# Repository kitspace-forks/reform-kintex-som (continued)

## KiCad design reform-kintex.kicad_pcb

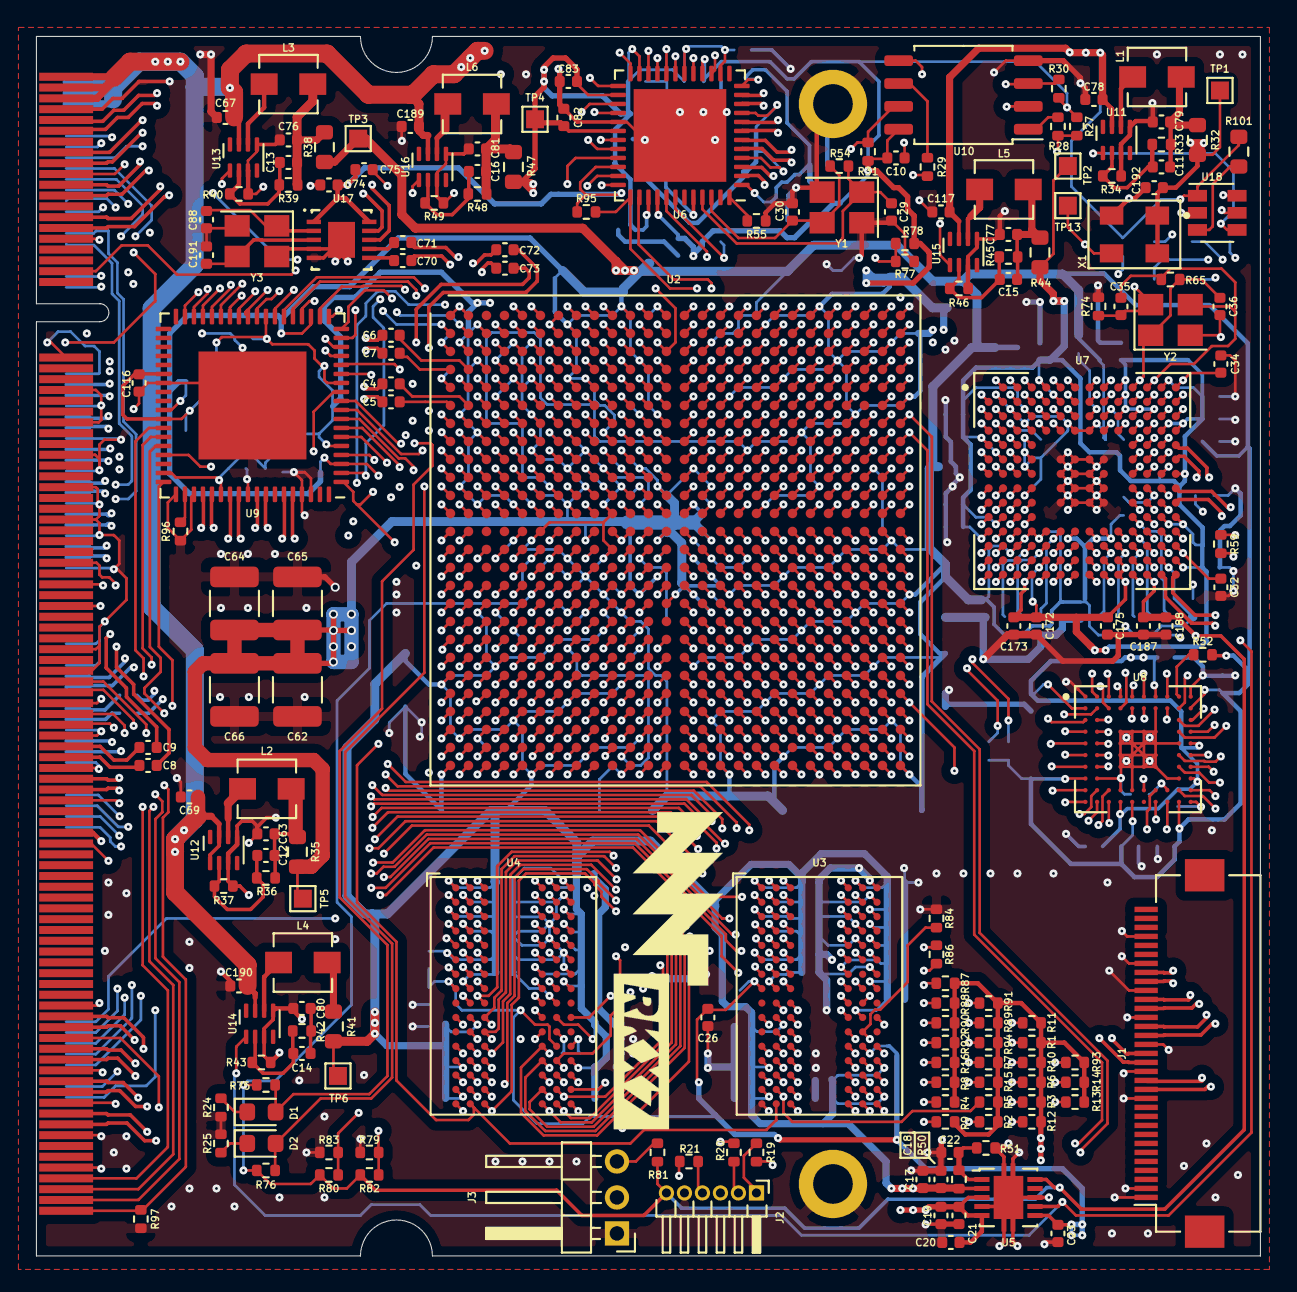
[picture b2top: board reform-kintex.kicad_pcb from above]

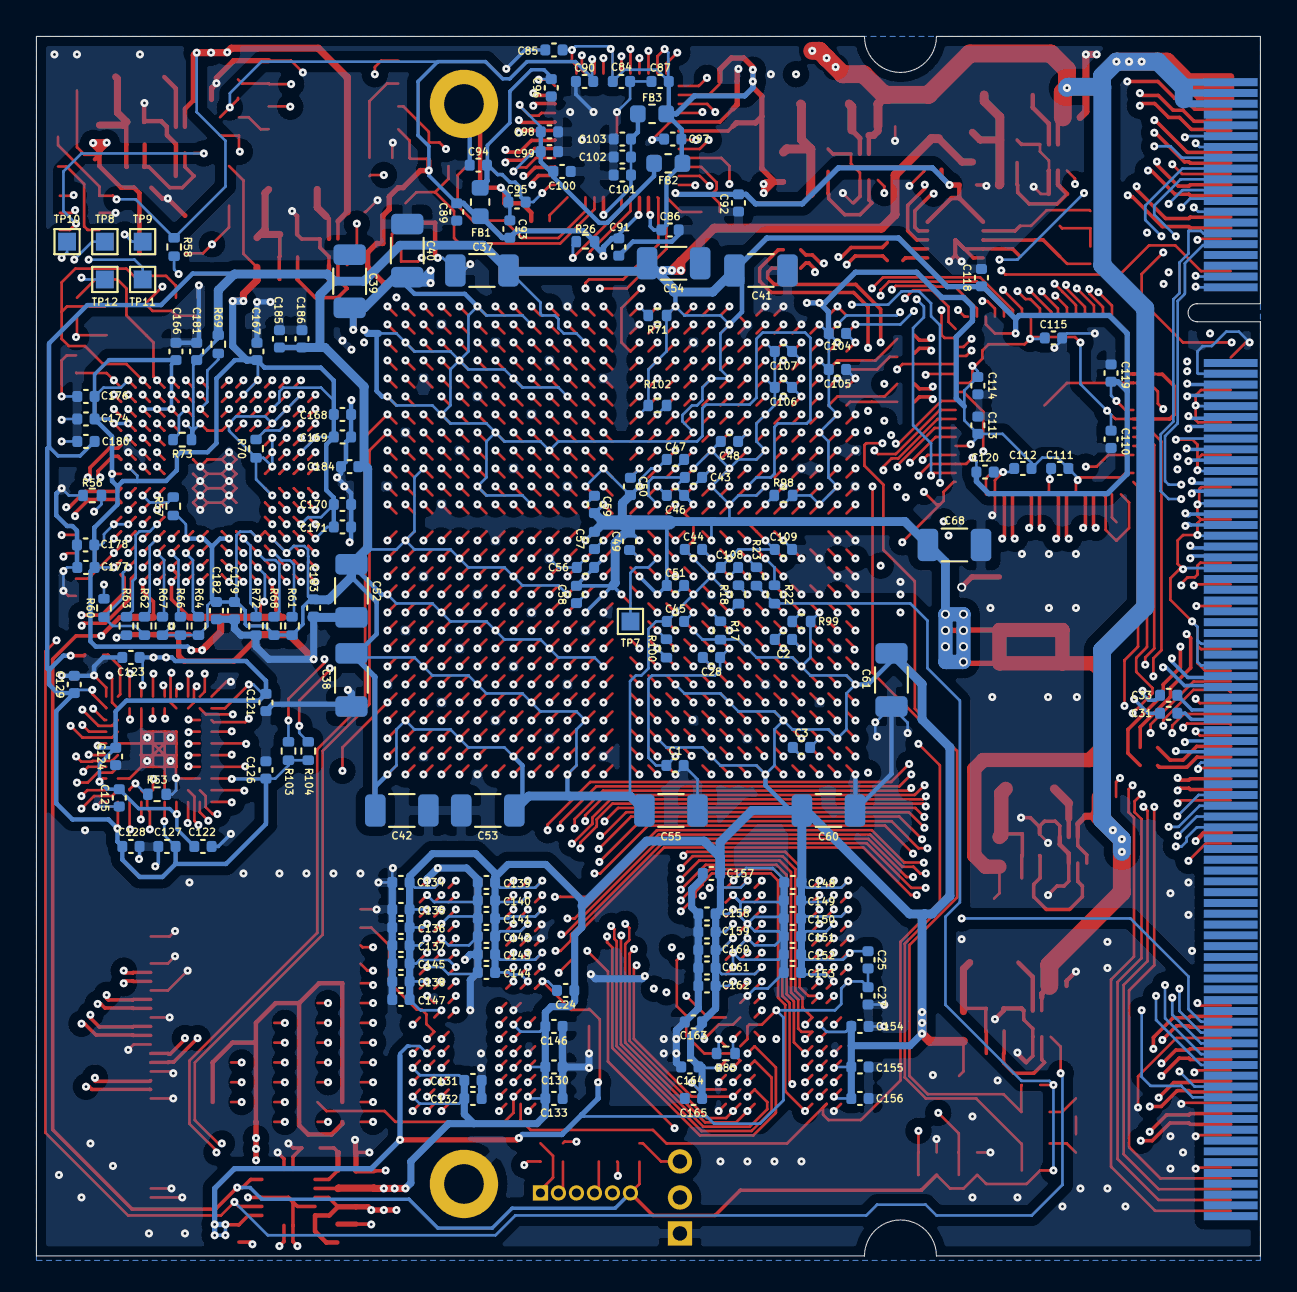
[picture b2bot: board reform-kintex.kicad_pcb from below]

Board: 8 copper layers, 68.0 x 67.8 mm, 348 parts (170 on the bottom side), 416 nets.

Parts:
C1, C2, C3, C4, C5, C6, C7, C8, C9, C10, C23, C28, C31, C33, C70, C71, C72, C73, C74, C83, C84, C85, C86, C87, C90, C91, C92, C95, C96, C99, C100, C102, C110, C111, C112, C113, C114, C115, C116, C118, C119, C120, C121, C122, C123, C124, C125, C126, C127, C128, C129, C130, C131, C132, C133, C134, C135, C136, C137, C138, C139, C140, C141, C142, C143, C144, C145, C146, C147, C148, C149, C150, C151, C152, C153, C154, C155, C156, C157, C158, C159, C160, C161, C162, C163, C164, C165, C167, C168, C169, C170, C171, C172, C173, C174, C175, C176, C177, C178, C180, C181, C182, C183, C184, C185, C186, C188, C192: 0.1uF; C_0402_1005Metric
C11, C12, C13, C14, C15, C16: 120p; C_0402_1005Metric
C17, C18, C19, C20, C21, C63, C76, C77, C79, C80, C81, C82, C89, C93, C94, C97, C98, C101: 10uF; C_0402_1005Metric
C22: 1nF; C_0402_1005Metric
C24, C25, C26, C27, C103: 10nF; C_0402_1005Metric
C29, C30, C35, C36, C88, C191: 22pF; C_0402_1005Metric
C32, C34: 4.7nF; C_0402_1005Metric
C37, C38, C39, C40, C41, C42, C60, C61, C68: 100uF; C_1206_3216Metric
C43, C44, C45, C46, C47, C48, C49, C50, C51, C56, C57, C58, C59, C67, C69, C75, C78, C104, C105, C106, C107, C108, C109, C117, C189, C190: 4.7uF; C_0402_1005Metric
C52, C53, C54, C55: 47uF; C_1206_3216Metric
C62, C64, C65, C66: 220uF; C_1210_3225Metric
C166, C179, C187: 1uF; C_0402_1005Metric
D1, D2: LED_Small; LED_0603_1608Metric
FB1, FB2, FB3: Ferrite_Bead_Small; L_0603_1608Metric
GFX1: MountingHole; mnt-rkx7
H1, H2: MountingHole_Pad; MountingHole_2.2mm_M2_DIN965_Pad
J1: Conn_01x33; Hirose_FH12-33S-0.5SH_1x33-1MP_P0.50mm_Horizontal
J2: JTAG_01x06; PinHeader_1x06_P1.00mm_Horizontal
J3: Conn_01x03_Male; PinHeader_1x03_P2.00mm_Horizontal
L1, L2, L3, L4, L5, L6: IHLP1212AEERR47M11; L_Vishay_IHLP-1212
R1, R2, R3, R4, R5, R6, R7, R8, R9, R10, R11, R12, R13, R14, R15, R16, R87, R88, R89, R90, R91, R92, R93, R94: 40; R_0402_1005Metric
R17, R18, R86, R99, R100: 80.6; R_0402_1005Metric
R19, R20, R21, R77, R98: 100; R_0402_1005Metric
R22, R26, R75, R95: 4.7k; R_0402_1005Metric
R23: ???; R_0402_1005Metric
R24, R25: 200; R_0402_1005Metric
R27: 2k2; R_0402_1005Metric
R28, R29, R79, R80, R81: 0; R_0402_1005Metric
R30, R31, R71, R102, R103, R104: 4k7; R_0402_1005Metric
R32, R35, R38, R41, R44, R47, R101: 0; R_0603_1608Metric
R33: 453k; R_0402_1005Metric
R34, R37, R40, R43, R46, R49: 100k_1%; R_0402_1005Metric
R36: 66.5k; R_0402_1005Metric
R39: 200k; R_0402_1005Metric
R42: 150k; R_0402_1005Metric
R45: 83.5k; R_0402_1005Metric
R48: 100k; R_0402_1005Metric
R50, R51, R52, R53, R56, R57, R97: 10k; R_0402_1005Metric
R54, R65: 1.8M; R_0402_1005Metric
R55: 12.1k; R_0402_1005Metric
R58: 90.9k 1%; R_0402_1005Metric
R59, R60: 10k 1%; R_0402_1005Metric
R61, R62, R63, R64, R66, R67, R68, R69, R70, R72, R73, R74, R78, R82, R83: DNP; R_0402_1005Metric
R76: 330; R_0402_1005Metric
R84, R85: 240 1%; R_0402_1005Metric
R96: 5.1k; R_0402_1005Metric
TP1, TP2, TP3, TP4, TP5, TP6, TP7, TP13: TestPoint; TestPoint_Pad_1.0x1.0mm
TP8: TUSBJ_TCK; TestPoint_Pad_1.0x1.0mm
TP9: TUSBJ_TMS; TestPoint_Pad_1.0x1.0mm
TP10: TUSBJ_TDI; TestPoint_Pad_1.0x1.0mm
TP11: TUSBJ_TRSTN; TestPoint_Pad_1.0x1.0mm
TP12: TUSBJ_TDO; TestPoint_Pad_1.0x1.0mm
U1: MNT Reform 2.0 SoM Socket; ddr2-sodimm200
U2: XC7K160T-FFG676; Xilinx_FFG676
U3, U4: IS43TR16512B-125KBLI; BGA-96_9.0x13.0mm_Layout2x3x16_P0.8mm
U5: TPS51200DRC; VSON-10-1EP_3x3mm_P0.5mm_EP1.65x2.4mm
U6: KSZ9031RNXCA; QFN-48-1EP_7x7mm_P0.5mm_EP5.15x5.15mm
U7: TUSB1310ZAY; BGA175C80P14X14_1200X1200X140
U8: TC358778XBG; BGA80C65P10X10_700X700X100
U9: SiI9022A; QFN-72-1EP_10x10mm_P0.5mm_EP6x6mm
U10: W25Q128JVS; SOIC-8_5.23x5.23mm_P1.27mm
U11, U12, U13, U14, U15, U16: TPS62823DLC; Texas_VSON-HR-8_1.5x2mm_P0.5mm
U17: Si52112-B5-GM2; Silicon_Labs-Si52112-B5-GM2-Level_B
U18: LM3880; SOT-23-6
X1: ASFLMB-100.000MHZ-XY-T; OSCDFN500X320X90-4N
Y1, Y3: ABM8G-25.000MHZ-18-D2Y-T; Crystal_SMD_3225-4Pin_3.2x2.5mm
Y2: ABM8G-20.000MHZ-18-D2Y-T; Crystal_SMD_3225-4Pin_3.2x2.5mm

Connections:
+1V0: C47.2, C48.2, C49.2, C50.2, C51.2, C56.2, C57.2, C58.2, C59.2, C62.2, C64.2, C65.2, C66.2, C68.2, C106.2, C107.2, R35.1, TP5.1, U2.C6, U2.E6, U2.G6, U2.J6, U2.J9, U2.K8, U2.K10, U2.K12, U2.K14, U2.L6, U2.L9, U2.L13, U2.L15, U2.M8, U2.M14, U2.N9, U2.N13, U2.N15, U2.P14, U2.R13, U2.R15, U2.T12, U2.T14, U2.U13, U2.U15
+1V1: C166.1, C167.1, C168.1, C169.1, C170.1, C171.1, C172.1, C173.1, C174.1, C175.1, C176.1, C177.1, C178.1, R44.1, TP2.1, U7.A5, U7.A10, U7.A13, U7.B6, U7.B10, U7.C4, U7.C10, U7.C11, U7.C12, U7.D13, U7.D14, U7.E1, U7.F2, U7.G13, U7.G14, U7.K2, U7.K13, U7.K14, U7.L1, U7.N5, U7.N10, U7.N14, U7.P4, U7.P10
+1V2: C82.2, C83.2, C84.2, C85.2, C86.2, C87.2, C97.2, C104.2, C105.2, C110.1, C111.1, C112.1, C113.1, C114.1, C115.1, C116.1, C121.1, C122.1, C123.1, C124.1, C125.1, FB2.2, FB3.2, R47.1, R98.2, TP4.1, U2.B3, U2.C2, U2.D3, U2.G2, U2.H3, U2.L2, U2.M3, U2.M5, U6.14, U6.18, U6.23, U6.26, U6.30, U6.39, U8.A7, U8.B1, U8.E10, U8.H10, U8.K4, U9.5, U9.12, U9.26, U9.42, U9.47, U9.53, U9.60
+1V5: C17.1, C18.1, C24.1, C25.1, C60.2, C61.2, C130.1, C131.1, C132.1, C133.1, C134.1, C135.1, C136.1, C137.1, C138.1, C139.1, C140.1, C141.1, C142.1, C143.1, C144.1, C145.1, C146.1, C147.1, C148.1, C149.1, C150.1, C151.1, C152.1, C153.1, C154.1, C155.1, C156.1, C157.1, C158.1, C159.1, C160.1, C161.1, C162.1, C163.1, C164.1, C165.1, R17.2, R41.1, R50.1, R99.2, TP6.1, U2.AA1, U2.AA11, U2.AB8, U2.AC5, U2.AD2, U2.AD12, U2.AE9, U2.AF6, U2.U3, U2.V10, U2.W7, U2.Y4, U3.A1, U3.A8, U3.B2, U3.C1, U3.C9, U3.D2, U3.D9, U3.E9, U3.F1, U3.G7, U3.H2, U3.H9, U3.K2, U3.K8, U3.N1, U3.N9, U3.R1, U3.R9, U4.A1, U4.A8, U4.B2, U4.C1, U4.C9, U4.D2, U4.D9, U4.E9, U4.F1, U4.G7, U4.H2, U4.H9, U4.K2, U4.K8, U4.N1, U4.N9, U4.R1, U4.R9, U5.2
+1V8: C37.2, C38.2, C41.2, C42.2, C43.2, C44.2, C45.2, C46.2, C52.2, C53.2, C54.2, C55.2, C108.2, C109.2, C118.1, C119.1, C120.1, C126.1, C127.1, C128.1, C129.1, C179.1, C180.1, C181.1, C182.1, C183.1, C184.1, C185.1, C186.1, R38.1, R52.1, R57.1, R61.1, R63.1, R64.1, R66.1, R67.1, R68.1, R69.1, R70.1, R71.1, R73.1, R102.1, R103.1, R104.1, TP3.1, U2.A11, U2.AA21, U2.AB18, U2.AC15, U2.AC25, U2.AD22, U2.AE19, U2.AF16, U2.AF26, U2.B8, U2.C15, U2.D12, U2.E8, U2.E9, U2.G13, U2.H10, U2.K24, U2.L11, U2.M10, U2.M12, U2.N6, U2.N25, U2.P8, U2.P10, U2.P22, U2.R9, U2.R19, U2.T8, U2.T10, U2.T16, U2.T26, U2.U11, U2.U23, U2.V20, U2.W17, U2.Y14, U2.Y24, U7.B2, U7.C3, U7.D4, U7.D7, U7.D8, U7.D9, U7.E4, U7.F4, U7.G4, U7.H4, U7.L4, U7.L5, U7.L7, U7.L8, U7.L9, U7.M3, U8.B10, U8.H1, U8.K5, U8.K9, U9.3, U9.21, U9.46
+3V3: C10.1, C39.2, C40.2, C74.2, C75.2, C89.2, C90.2, C91.2, C92.2, C93.2, C187.1, C188.1, C192.1, FB1.2, J2.6, R22.1, R23.1, R26.1, R27.1, R30.1, R31.1, R32.1, R75.1, R76.1, R77.1, R79.1, R80.1, R81.1, R95.1, TP1.1, U2.A21, U2.B18, U2.C25, U2.D22, U2.E19, U2.F16, U2.F26, U2.G23, U2.H20, U2.J17, U2.L7, U2.L21, U2.M18, U2.T6, U5.10, U6.16, U6.34, U6.40, U7.P12, U10.8, U17.1, U17.10, X1.1, X1.4
+5V: C67.2, C69.2, C78.2, C117.2, C189.2, C190.2, R58.2, R101.1, U1.1, U1.2, U1.3, U1.4, U1.5, U1.6, U11.7, U12.1, U12.7, U13.7, U14.7, U15.7, U16.7, U18.1
/RAM/PCIE2_GTX_CLK_HOST_N: C71.2, U2.D5
/RAM/PCIE2_GTX_CLK_HOST_P: C70.2, U2.D6
/RAM/PCIE2_GTX_CLK_N: C73.2, U2.F5
/RAM/PCIE2_GTX_CLK_P: C72.2, U2.F6
/RAM/USB1TXN: C31.2, U7.H14
/RAM/USB1TXP: C33.2, U7.J14
/RAM/USB2_GTX_N: C8.2, U2.B1
/RAM/USB2_GTX_P: C9.2, U2.B2
BACKLIGHT_EN: U1.105, U2.B16
BACKLIGHT_PWM: U1.164, U2.K16
CCLK: R29.2, U2.C8
CLK_100MHZ: TP13.1, U2.F22, X1.3
DAC_BCLK: U1.170, U2.L17
DAC_DIN: U1.166, U2.K17
DAC_DOUT: U1.178, U2.M17
DAC_MCLK: U1.176, U2.L18
DAC_RXFS: U1.168, U2.K18
DAC_SCL: U1.101, U2.H26
DAC_SDA: U1.103, U2.G26
DAC_TXFS: U1.172, U2.M16
DISP1_CLK: U2.C12, U9.22
DISP1_DE: U2.D10, U9.33
DISP1_HS: U2.D11, U9.34
DISP1_RGB0: U2.E10, U9.32
DISP1_RGB1: U2.D8, U9.31
DISP1_RGB2: U2.F9, U9.30
DISP1_RGB3: U2.F8, U9.29
DISP1_RGB4: U2.A9, U9.28
DISP1_RGB5: U2.A8, U9.27
DISP1_RGB6: U2.B9, U9.25
DISP1_RGB7: U2.D9, U9.24
DISP1_RGB8: U2.F14, U9.23
DISP1_RGB9: U2.C9, U9.20
DISP1_RGB10: U2.G14, U9.19
DISP1_RGB11: U2.F10, U9.18
DISP1_RGB12: U2.H14, U9.17
DISP1_RGB13: U2.G11, U9.16
DISP1_RGB14: U2.H11, U9.15
DISP1_RGB15: U2.G9, U9.14
DISP1_RGB16: U2.H13, U9.13
DISP1_RGB17: U2.G10, U9.11
DISP1_RGB18: U2.J13, U9.10
DISP1_RGB19: U2.H12, U9.9
DISP1_RGB20: U2.J10, U9.8
DISP1_RGB21: U2.H8, U9.7
DISP1_RGB22: U2.H9, U9.6
DISP1_RGB23: U2.J11, U9.4
DISP1_SCL: R102.2, U1.107, U2.G12, U9.1
DISP1_SDA: R71.2, U1.109, U2.A13, U9.2
DISP1_VS: U2.E11, U9.35
DISP2_DE: U2.AA15, U8.J7
DISP2_HS: U2.AB15, U8.K8
DISP2_PCLK: U2.AC18, U8.J6
DISP2_RGB0: U2.AF15, U8.J3
DISP2_RGB1: U2.AF14, U8.K3
DISP2_RGB2: U2.AE16, U8.J2
DISP2_RGB3: U2.AE15, U8.K2
DISP2_RGB4: U2.AE17, U8.J1
DISP2_RGB5: U2.AF17, U8.K1
DISP2_RGB6: U2.AA14, U8.G2
DISP2_RGB7: U2.AF18, U8.G1
DISP2_RGB8: U2.AD15, U8.F2
DISP2_RGB9: U2.AE18, U8.F1
DISP2_RGB10: U2.AD16, U8.E2
DISP2_RGB11: U2.AF19, U8.E1
DISP2_RGB12: U2.AC16, U8.D2
DISP2_RGB13: U2.AD14, U8.D1
DISP2_RGB14: U2.AC17, U8.C2
DISP2_RGB15: U2.AC14, U8.C1
DISP2_RGB16: U2.AB14, U8.B2
DISP2_RGB17: U2.AA17, U8.A2
DISP2_RGB18: U2.Y15, U8.B3
DISP2_RGB19: U2.AA18, U8.A3
DISP2_RGB20: U2.Y16, U8.B4
DISP2_RGB21: U2.AB17, U8.A4
DISP2_RGB22: U2.AF20, U8.B5
DISP2_RGB23: U2.AD20, U8.A5
DISP2_SCL: R104.2, U2.Y26, U8.A8
DISP2_SDA: R103.2, U2.W26, U8.B8
DISP2_VS: U2.AB16, U8.K7
DSI_CLK_N: J1.19, U8.F10
DSI_CLK_P: J1.20, U8.F9
DSI_D0_N: J1.25, U8.J10
DSI_D0_P: J1.26, U8.J9
DSI_D1_N: J1.22, U8.G10
DSI_D1_P: J1.23, U8.G9
DSI_D2_N: J1.16, U8.D10
DSI_D2_P: J1.17, U8.D9
DSI_D3_N: J1.13, U8.C10
DSI_D3_P: J1.14, U8.C9
DSI_RST_N: U2.AB26, U8.B9
EDP_RESETn: U1.38, U2.C14
EN_VAUX: U15.1, U18.6
EN_VDDR: U5.7, U14.1, U18.5
EN_VIO: U11.1, U13.1, U16.1, U18.4
ETH0_A+: U1.29, U6.2
ETH0_A-: U1.27, U6.3
ETH0_B+: U1.23, U6.5
ETH0_B-: U1.21, U6.6
ETH0_C+: U1.17, U6.7
ETH0_C-: U1.15, U6.8
ETH0_D+: U1.11, U6.10
ETH0_D-: U1.9, U6.11
ETH0_LED_LINK1: U1.83, U6.17
ETH0_LED_RX: U1.79, U6.15
ETH_INT_N: U2.E16, U6.38
ETH_MDC: U2.E17, U6.36
ETH_MDIO: R95.2, U2.E15, U6.37
ETH_REF_CLK: U2.F17, U6.41
ETH_RST_N: R26.2, U2.G17, U6.42
ETH_RX_CLK: U2.D18, U6.35
ETH_RX_D0: U2.J15, U6.32
ETH_RX_D1: U2.J16, U6.31
ETH_RX_D2: U2.F20, U6.28
ETH_RX_D3: U2.D20, U6.27
ETH_RX_DV: U2.F15, U6.33
ETH_TX_CLK: U2.E18, U6.24
ETH_TX_D0: U2.H18, U6.19
ETH_TX_D1: U2.H17, U6.20
ETH_TX_D2: U2.G19, U6.21
ETH_TX_D3: U2.F18, U6.22
ETH_TX_EN: U2.D19, U6.25
ETH_VDDA: C94.2, C95.2, C96.2, FB1.1, U6.1, U6.12
ETH_VDDL: C98.2, C99.2, C100.2, FB2.1, U6.4, U6.9
ETH_VDDL_PLL: C101.2, C102.2, C103.2, FB3.1, U6.44
FCS_B: R27.2, R28.2, U2.C23
GND: C1.1, C2.1, C3.1, C10.2, C17.2, C18.2, C19.2, C20.2, C21.2, C22.2, C23.2, C26.2, C27.2, C28.1, C29.2, C30.2, C32.2, C34.2, C37.1, C38.1, C39.1, C40.1, C41.1, C42.1, C43.1, C44.1, C45.1, C46.1, C47.1, C48.1, C49.1, C50.1, C51.1, C52.1, C53.1, C54.1, C55.1, C56.1, C57.1, C58.1, C59.1, C60.1, C61.1, C62.1, C63.2, C64.1, C65.1, C66.1, C67.1, C68.1, C69.1, C74.1, C75.1, C76.2, C77.2, C78.1, C79.2, C80.2, C81.2, C82.1, C83.1, C84.1, C85.1, C86.1, C87.1, C88.2, C89.1, C90.1, C91.1, C92.1, C93.1, C94.1, C95.1, C96.1, C97.1, C98.1, C99.1, C100.1, C101.1, C102.1, C103.1, C104.1, C105.1, C106.1, C107.1, C108.1, C109.1, C110.2, C111.2, C112.2, C113.2, C114.2, C115.2, C116.2, C117.1, C118.2, C119.2, C120.2, C121.2, C122.2, C123.2, C124.2, C125.2, C126.2, C127.2, C128.2, C129.2, C130.2, C131.2, C132.2, C133.2, C134.2, C135.2, C136.2, C137.2, C138.2, C139.2, C140.2, C141.2, C142.2, C143.2, C144.2, C145.2, C146.2, C147.2, C148.2, C149.2, C150.2, C151.2, C152.2, C153.2, C154.2, C155.2, C156.2, C157.2, C158.2, C159.2, C160.2, C161.2, C162.2, C163.2, C164.2, C165.2, C166.2, C167.2, C168.2, C169.2, C170.2, C171.2, C172.2, C173.2, C174.2, C175.2, C176.2, C177.2, C178.2, C179.2, C180.2, C181.2, C182.2, C183.2, C184.2, C185.2, C186.2, C187.2, C188.2, C189.1, C190.1, C191.2, C192.2, H1.1, H2.1, J1.1, J1.2, J1.12, J1.15, J1.18, J1.21, J1.24, J1.27, J1.30, J2.5, J3.1, R18.1, R24.1, R25.1, R34.2, R37.2, R40.2, R43.2, R46.2, R49.2, R51.1, R53.2, R55.2, R56.1, R60.1, R62.1, R72.1, R74.1, R78.2, R82.2, R83.2, R84.2, R85.2, R96.1, R97.2, R100.1, U1.7, U1.19, U1.31, U1.41, U1.44, U1.47, U1.50, U1.53, U1.56, U1.59, U1.62, U1.65, U1.68, U1.71, U1.74, U1.80, U1.94, U1.95, U1.98, U1.99, U1.110, U1.111, U1.116, U1.117, U1.123, U1.129, U1.161, U1.167, U1.173, U1.179, U1.185, U1.191, U2.A1, U2.A2, U2.A5, U2.A6, U2.A7, U2.A16, U2.A26, U2.AA6, U2.AA16, U2.AA26, U2.AB3, U2.AB13, U2.AB23, U2.AC10, U2.AC20, U2.AD7, U2.AD17, U2.AE4, U2.AE14, U2.AE24, U2.AF1, U2.AF11, U2.AF21, U2.B4, U2.B7, U2.B13, U2.B23, U2.C1, U2.C5, U2.C7, U2.C10, U2.C20, U2.D4, U2.D7, U2.D17, U2.E1, U2.E2, U2.E5, U2.E7, U2.E14, U2.E24, U2.F3, U2.F4, U2.F7, U2.F11, U2.F21, U2.G1, U2.G5, U2.G8, U2.G18, U2.H4, U2.H7, U2.H15, U2.H25, U2.J1, U2.J2, U2.J5, U2.J12, U2.J22, U2.K3, U2.K4, U2.K7, U2.K9, U2.K11, U2.K13, U2.K19, U2.L1, U2.L5, U2.L10, U2.L12, U2.L14, U2.L16, U2.L26, U2.M4, U2.M7, U2.M9, U2.M13, U2.M15, U2.M23, U2.N1, U2.N2, U2.N5, U2.N7, U2.N10, U2.N11, U2.N12, U2.N14, U2.N20, U2.P3, U2.P4, U2.P9, U2.P11, U2.P13, U2.P15, U2.P17, U2.R1, U2.R2, U2.R5, U2.R8, U2.R10, U2.R11, U2.R12, U2.R14, U2.R24, U2.T1, U2.T3, U2.T4, U2.T9, U2.T11, U2.T13, U2.T15, U2.T21, U2.U8, U2.U10, U2.U12, U2.U14, U2.U18, U2.V5, U2.V15, U2.V25, U2.W2, U2.W12, U2.W22, U2.Y9, U2.Y19, U3.A9, U3.B1, U3.B3, U3.B9, U3.D1, U3.D8, U3.E1, U3.E2, U3.E8, U3.F9, U3.G1, U3.G9, U3.J2, U3.J8, U3.M1, U3.M9, U3.P1, U3.P9, U3.T1, U3.T9, U4.A9, U4.B1, U4.B3, U4.B9, U4.D1, U4.D8, U4.E1, U4.E2, U4.E8, U4.F9, U4.G1, U4.G9, U4.J2, U4.J8, U4.M1, U4.M9, U4.P1, U4.P9, U4.T1, U4.T9, U5.4, U5.8, U5.11, U6.29, U6.49, U7.B11, U7.B13, U7.B14, U7.D12, U7.E13, U7.F6, U7.F7, U7.F8, U7.F9, U7.F12, U7.F13, U7.G6, U7.G7, U7.G8, U7.G9, U7.G12, U7.H6, U7.H7, U7.H8, U7.H9, U7.H13, U7.J6, U7.J7, U7.J8, U7.J9, U7.J13, U7.K12, U7.L12, U7.M12, U7.M13, U7.N13, U8.A1, U8.A10, U8.B7, U8.D4, U8.D5, U8.D6, U8.D7, U8.E4, U8.E5, U8.E6, U8.E7, U8.E9, U8.F4, U8.F5, U8.F6, U8.F7, U8.G4, U8.G5, U8.G6, U8.G7, U8.H2, U8.H9, U8.J4, U8.J5, U8.K10, U9.43, U9.55, U9.57, U9.63, U9.69, U9.70, U9.73, U10.4, U11.3, U11.5, U12.3, U12.5, U13.3, U13.5, U14.3, U14.5, U15.3, U15.5, U16.3, U16.5, U17.4, U17.5, U18.2, X1.2, Y1.2, Y1.4, Y3.2, Y3.4
HDMI_CEC: U1.197, U9.50
HDMI_CLK+: U1.165, U9.58
HDMI_CLK-: U1.163, U9.59
HDMI_D0+: U1.171, U9.62
HDMI_D0-: U1.169, U9.61
HDMI_D1+: U1.177, U9.65
HDMI_D1-: U1.175, U9.64
HDMI_D2+: U1.183, U9.68
HDMI_D2-: U1.181, U9.67
HDMI_HPD: R97.1, U1.199, U9.54
HDMI_RST_N: U2.C13, U9.51
HDMI_SCL: U1.195, U9.49
HDMI_SDA: U1.193, U9.48
MODE0: R79.2, R82.1, U2.T5
MODE1: R80.2, R83.1, U2.T2
MODE2: J3.2, U2.P5
unnamed: C4.2, U2.F2
unnamed: C5.2, U2.F1
unnamed: C6.2, U2.D2
unnamed: C7.2, U2.D1
unnamed: C11.1, C79.1, L1.2, R32.2, R33.1
unnamed: C11.2, R33.2, R34.1, U11.2
unnamed: C12.1, C63.1, L2.2, R35.2, R36.1
unnamed: C12.2, R36.2, R37.1, U12.2
unnamed: C13.1, C76.1, L3.2, R38.2, R39.1
unnamed: C13.2, R39.2, R40.1, U13.2
unnamed: C14.1, C80.1, L4.2, R41.2, R42.1
unnamed: C14.2, R42.2, R43.1, U14.2
unnamed: C15.1, C77.1, L5.2, R44.2, R45.1
unnamed: C15.2, R45.2, R46.1, U15.2
unnamed: C16.1, C81.1, L6.2, R47.2, R48.1
unnamed: C16.2, R48.2, R49.1, U16.2
unnamed: C22.1, R50.2, R51.2, U5.1
unnamed: C29.1, R54.2, U6.45, Y1.1
unnamed: C30.1, R54.1, U6.46, Y1.3
unnamed: C32.1, U7.M14
unnamed: C34.1, U7.A14
unnamed: C35.1, R65.1, U7.A12, Y2.3
unnamed: C36.1, R65.2, U7.A11, Y2.1
unnamed: C88.1, U17.2, Y3.1
unnamed: C191.1, U17.3, Y3.3
unnamed: D1.1, R24.2
unnamed: D1.2, R75.2, U2.G7
unnamed: D2.1, R25.2
unnamed: D2.2, R76.2, U2.J7
unnamed: J2.1, R19.2
unnamed: J2.2, R20.2
unnamed: J2.3, U2.R7
unnamed: J2.4, R21.2
unnamed: J3.3, R81.2
unnamed: L1.1, U11.6
unnamed: L2.1, U12.6
unnamed: L3.1, U13.6
unnamed: L4.1, U14.6
unnamed: L5.1, U15.6
unnamed: L6.1, U16.6
unnamed: R17.1, U2.U9
unnamed: R18.2, U2.T7
unnamed: R19.1, U2.N8
unnamed: R20.1, U2.R6
unnamed: R21.1, U2.L8
unnamed: R23.2, U2.P7
unnamed: R28.1, U10.1
unnamed: R29.1, U10.6
unnamed: R52.2, U8.A9
unnamed: R53.1, U8.J8
unnamed: R55.1, U6.48
unnamed: R56.2, U7.J12
unnamed: R57.2, U7.H12
unnamed: R58.1, R60.2, U7.N12
unnamed: R59.1, U7.L14
unnamed: R59.2, U7.L13
unnamed: R61.2, U7.M4
unnamed: R62.2, U7.L11
unnamed: R63.2, U7.K11
unnamed: R64.2, U7.M9
unnamed: R66.2, U7.M10
unnamed: R67.2, U7.M11
unnamed: R68.2, U7.M5
unnamed: R69.2, U7.C8
unnamed: R70.2, U7.D3
unnamed: R72.2, U7.L6
unnamed: R73.2, U7.C9
unnamed: R84.1, U3.L8
unnamed: R85.1, U4.L8
unnamed: R96.2, U9.56
unnamed: R98.1, U2.M6
unnamed: R99.1, U2.U4
unnamed: R100.2, U2.V12
unnamed: R101.2, U18.3
unnamed: TP8.1, U7.G11
unnamed: TP9.1, U7.D11
unnamed: TP10.1, U7.E11
unnamed: TP11.1, U7.E12
unnamed: TP12.1, U7.F11
PCIE1_CLK_HOST_N: C71.1, U17.7
PCIE1_CLK_HOST_P: C70.1, U17.6
PCIE1_CLK_N: U1.60, U17.9
PCIE1_CLK_P: U1.58, U17.8
PCIE1_RESETn: U1.37, U2.A17
PCIE1_RX_N: U1.54, U2.G3
PCIE1_RX_P: U1.52, U2.G4
PCIE1_TX_N: C5.1, U1.48
PCIE1_TX_P: C4.1, U1.46
PCIE2_CLK_N: C73.1, U1.66
PCIE2_CLK_P: C72.1, U1.64
PCIE2_RESETn: U1.24, U2.A18
PCIE2_RX_N: U1.78, U2.E3
PCIE2_RX_P: U1.76, U2.E4
PCIE2_TX_N: C7.1, U1.72
PCIE2_TX_P: C6.1, U1.70
PUDC_B: R77.2, R78.1, U2.B25
QSPI_DQ0: U2.B24, U10.5
QSPI_DQ1: U2.A25, U10.2
QSPI_DQ2: R30.2, U2.B22, U10.3
QSPI_DQ3: R31.2, U2.A22, U10.7
RAM_A0: R16.2, U2.AC8, U3.N3, U4.N3
RAM_A1: R8.2, U2.AA7, U3.P7, U4.P7
RAM_A2: R15.2, U2.AA8, U3.P3, U4.P3
RAM_A3: R7.2, U2.AF7, U3.N2, U4.N2
RAM_A4: R14.2, U2.AE7, U3.P8, U4.P8
RAM_A5: R6.2, U2.AC11, U3.P2, U4.P2
RAM_A6: R13.2, U2.V9, U3.R8, U4.R8
RAM_A7: R5.2, U2.Y10, U3.R2, U4.R2
RAM_A8: R12.2, U2.AB11, U3.T8, U4.T8
RAM_A9: R4.2, U2.Y7, U3.R3, U4.R3
RAM_A10: R11.2, U2.Y8, U3.L7, U4.L7
RAM_A11: R3.2, U2.V11, U3.R7, U4.R7
RAM_A12: R10.2, U2.V8, U3.N7, U4.N7
RAM_A13: R2.2, U2.W11, U3.T3, U4.T3
RAM_A14: R9.2, U2.Y11, U3.T7, U4.T7
RAM_A15: R1.2, U2.V7, U3.M7, U4.M7
RAM_BA0: R92.2, U2.AC7, U3.M2, U4.M2
RAM_BA1: R93.2, U2.AB7, U3.N8, U4.N8
RAM_BA2: R94.2, U2.AB9, U3.M3, U4.M3
RAM_CAS#: R88.2, U2.AD8, U3.K3, U4.K3
RAM_CK+: R86.2, U2.W10, U3.J7, U4.J7
RAM_CK-: R86.1, U2.W9, U3.K7, U4.K7
RAM_CKE: R91.2, U2.AB12, U3.K9, U4.K9
RAM_CS#: R90.2, U2.AD9, U3.L2, U4.L2
RAM_D0: U2.V4, U3.E3
RAM_D1: U2.W3, U3.F7
RAM_D2: U2.U5, U3.F2
RAM_D3: U2.Y1, U3.F8
RAM_D4: U2.U7, U3.H3
RAM_D5: U2.W1, U3.H8
RAM_D6: U2.V6, U3.G2
RAM_D7: U2.V2, U3.H7
RAM_D8: U2.Y2, U3.D7
RAM_D9: U2.U1, U3.C3
RAM_D10: U2.AA3, U3.C8
RAM_D11: U2.V3, U3.C2
RAM_D12: U2.AC2, U3.A7
RAM_D13: U2.U2, U3.A2
RAM_D14: U2.AB2, U3.B8
RAM_D15: U2.V1, U3.A3
RAM_D16: U2.AA4, U4.E3
RAM_D17: U2.AB4, U4.H3
RAM_D18: U2.AC4, U4.F7
RAM_D19: U2.AC3, U4.F2
RAM_D20: U2.AC6, U4.F8
RAM_D21: U2.Y6, U4.H8
RAM_D22: U2.Y5, U4.G2
RAM_D23: U2.AD6, U4.H7
RAM_D24: U2.AD1, U4.C3
RAM_D25: U2.AE1, U4.A2
RAM_D26: U2.AE3, U4.B8
RAM_D27: U2.AE2, U4.A3
RAM_D28: U2.AE6, U4.A7
RAM_D29: U2.AE5, U4.D7
RAM_D30: U2.AF3, U4.C8
RAM_D31: U2.AF2, U4.C2
RAM_DM0: U2.U6, U3.E7
RAM_DM1: U2.AD5, U3.D3
RAM_DM2: U2.AB6, U4.E7
RAM_DM3: U2.AD4, U4.D3
RAM_DQS0+: U2.W6, U3.F3
RAM_DQS0-: U2.W5, U3.G3
RAM_DQS1+: U2.AB1, U3.C7
RAM_DQS1-: U2.AC1, U3.B7
RAM_DQS2+: U2.AA5, U4.F3
RAM_DQS2-: U2.AB5, U4.G3
RAM_DQS3+: U2.AF5, U4.C7
RAM_DQS3-: U2.AF4, U4.B7
RAM_ODT: U2.AC12, U3.K1, U4.K1
RAM_RAS#: R87.2, U2.AA9, U3.J3, U4.J3
RAM_RESET#: U2.AA2, U3.T2, U4.T2
RAM_WE#: R89.2, U2.AC9, U3.L3, U4.L3
SD2_CD: U1.26, U2.A10
SD2_CLK: U1.22, U2.C11
SD2_CMD: U1.20, U2.A15
SD2_DATA0: U1.12, U2.A14
SD2_DATA1: U1.14, U2.B10
SD2_DATA2: U1.16, U2.A12
SD2_DATA3: U1.18, U2.B15
SOC_RESETn: R22.2, U1.87, U2.P6
TUSB_CLKOUT: U2.Y23, U7.D10
TUSB_ENAB: U2.AD25, U7.L10
TUSB_PCLK: U2.R21, U7.A6
TUSB_PDOWN0: U2.N23, U7.H3
TUSB_PDOWN1: U2.AD26, U7.G3
TUSB_PHYRESETN: U2.P23, U7.J3
TUSB_PHY_STATUS: U2.T22, U7.E3
TUSB_PWRPRESENT: U2.AE22, U7.H11
TUSB_RESETN: U2.AF25, U7.J11
TUSB_RX_D0: U2.R20, U7.E2
TUSB_RX_D1: U2.M25, U7.D2
TUSB_RX_D2: U2.M26, U7.D1
TUSB_RX_D3: U2.R18, U7.C1
TUSB_RX_D4: U2.T23, U7.C2
TUSB_RX_D5: U2.T25, U7.B1
TUSB_RX_D6: U2.N19, U7.A2
TUSB_RX_D7: U2.P18, U7.A3
TUSB_RX_D8: U2.N18, U7.B3
TUSB_RX_D9: U2.T19, U7.A4
TUSB_RX_D10: U2.L24, U7.B4
TUSB_RX_D11: U2.K25, U7.B5
TUSB_RX_D12: U2.AE26, U7.B8
TUSB_RX_D13: U2.AE25, U7.A8
TUSB_RX_D14: U2.AF23, U7.A9
TUSB_RX_D15: U2.AF24, U7.B9
TUSB_RX_ELECIDLE: U2.AE23, U7.F3
TUSB_RX_K0: U2.K26, U7.A7
TUSB_RX_K1: U2.L25, U7.B7
TUSB_RX_STAT0: U2.M24, U7.C5
TUSB_RX_STAT1: U2.N17, U7.C6
TUSB_RX_STAT2: U2.P16, U7.C7
TUSB_RX_VALID: U2.R26, U7.F1
TUSB_TXCLK: U2.N21, U7.K1
TUSB_TX_D0: U2.R25, U7.P5
TUSB_TX_D1: U2.P26, U7.N4
TUSB_TX_D2: U2.T18, U7.P3
TUSB_TX_D3: U2.R17, U7.N3
TUSB_TX_D4: U2.U19, U7.P2
TUSB_TX_D5: U2.T20, U7.N2
TUSB_TX_D6: U2.R23, U7.P1
TUSB_TX_D7: U2.P25, U7.N1
TUSB_TX_D8: U2.R22, U7.M1
TUSB_TX_D9: U2.P24, U7.M2
TUSB_TX_D10: U2.N26, U7.L2
TUSB_TX_D11: U2.U20, U7.L3
TUSB_TX_D12: U2.M20, U7.J2
TUSB_TX_D13: U2.M19, U7.H1
TUSB_TX_D14: U2.M22, U7.H2
TUSB_TX_D15: U2.AD23, U7.G2
TUSB_TX_DATAK0: U2.M21, U7.J1
TUSB_TX_DATAK1: U2.AC22, U7.G1
TUSB_TX_DETRX_LPBK: U2.AB22, U7.M6
TUSB_TX_ELECIDLE: U2.N24, U7.K3
TUSB_ULPI_CLK: U2.AF22, U7.P11
TUSB_ULPI_D0: U2.AC21, U7.N9
TUSB_ULPI_D1: U2.AD21, U7.P9
TUSB_ULPI_D2: U2.AB21, U7.P8
TUSB_ULPI_D3: U2.Y20, U7.N8
TUSB_ULPI_D4: U2.W20, U7.P7
TUSB_ULPI_D5: U2.U17, U7.N7
TUSB_ULPI_D6: U2.T17, U7.P6
TUSB_ULPI_D7: U2.R16, U7.N6
TUSB_ULPI_DIR: U2.AD24, U7.M7
TUSB_ULPI_NXT: U2.AE21, U7.N11
TUSB_ULPI_STP: U2.Y21, U7.M8
TUSB_VSSOSC: C35.2, C36.2, R74.2, U7.B12, Y2.2, Y2.4
UART1_RX: U1.126, U2.C18
UART1_TX: U1.128, U2.D15
UART2_RX: U1.122, U2.C16
UART2_TX: U1.124, U2.C17
UART3_RX: U1.32, U2.G16
UART3_TX: U1.30, U2.H16
USB1_DN: U1.100, U7.P13
USB1_DP: U1.102, U7.P14
USB1_RX_N: U1.112, U7.E14
USB1_RX_P: U1.114, U7.F14
USB1_TX_N: C31.1, U1.106
USB1_TX_P: C33.1, U1.108
USB2_RX_N: U1.121, U2.C3
USB2_RX_P: U1.119, U2.C4
USB2_TX_N: C8.1, U1.115
USB2_TX_P: C9.1, U1.113
USB_RESETn: U1.131, U2.D13
VAA: TP7.1, U2.P12
VTTREF: C1.2, C2.2, C3.2, C23.1, C24.2, C25.2, C26.1, C27.1, C28.2, U2.AD3, U2.AE11, U2.W4, U2.W8, U3.H1, U3.M8, U4.H1, U4.M8, U5.6
Vtt: C19.1, C20.1, C21.1, R1.1, R2.1, R3.1, R4.1, R5.1, R6.1, R7.1, R8.1, R9.1, R10.1, R11.1, R12.1, R13.1, R14.1, R15.1, R16.1, R87.1, R88.1, R89.1, R90.1, R91.1, R92.1, R93.1, R94.1, U5.3, U5.5

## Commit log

2021-04-02 initial WIP commit
2021-04-02 add some (temporary) datasheets and docs
2021-04-08 some work on 6 power supplies, SPI flash
2021-04-09 switch to TC358778XBG, some more connections here and there
2021-04-24 some more TUSB signals connected
2021-04-24 more TUSB noodling
2021-05-09 finish first draft of TUSB connectivity
2021-05-27 more DDR3 routing
2021-05-28 ram bus termination
2021-05-28 DSI and some USB routing
2021-06-03 more routing, esp. ethernet
2021-06-04 more routing, bunch of fpga bypass caps, logo
2021-06-06 schematics: add many decoupling caps
2021-06-09 ram bypass caps placed
2021-06-16 place lots of caps; place some power supplies
2021-06-17 place all components
2021-06-20 more routing
2021-07-05 more routing: 215 to go
2021-07-06 add power sequencer, main clock, some missing resets, more routing (198)
2021-07-07 more routing (39)
2021-07-07 fully routed
2021-07-07 connect some missing i2c signals, backlight_en
2021-07-07 silkscreen cleanup, 3d models, some footprint fixes
2021-07-07 actual 3d models and footprints
2021-07-08 WIP ddr data and address groups length matching
2021-07-09 ddr3 length matching
2021-07-09 card edge: remove paste from pads
2021-07-09 reconnect remaining pads
2021-07-09 DRC, polishing, bugfixes, badge
2021-07-09 add readme, schematics pdf, image
2021-07-09 readme: fix images
2021-07-09 readme: add links
2021-07-09 readme: typo
2021-07-10 pcb: fix some ram trace lengths
2021-07-10 add validated MIG UCF; requires a few DQ signal changes
2021-07-11 WIP adjust ddr trace widths; prepare some TODOs for errors found with vivado
2021-07-11 reroute some DDR signals, tweak more track widths
2021-07-11 DDR length matching double checked/fixed
2021-07-11 TUSB: fix VDDA1P8
2021-07-12 reroute all diff pairs
2021-07-12 snapshot before tusb length matching
2021-07-12 final tweaks for first fabbing
2021-07-12 add d-1 gerbers
2022-01-27 add some notes, gerbes and BOM after first D-1 bringup
2022-08-16 snapshot before touching RAM
2022-08-18 ddr new routing snapshot before length matching
2022-08-18 ddr new routing snapshot after length matching
2022-08-19 snapshot with tuned ddr address/command group
2022-08-19 snapshot with tuned ddr double checked
2022-08-19 snapshot after cleanup
2022-08-19 first finished layout of rev 2
2022-09-08 pcb: clean up D-2 BOM
2022-10-03 schematic: minor cleanups
2022-10-03 BOM update
2022-10-03 clean up schematics
2022-10-03 add ANX9807 footprint
2022-10-03 add images
2022-10-03 reduce image sizes
2022-10-03 add litex patches
2022-10-03 add linux and litex patches
2022-10-03 add DTS files for single and dual core vexriscv
2022-10-03 add bitfile
2022-10-03 add RGB-eDP adapter kicad files
2022-10-03 add eDP adapter schematics
